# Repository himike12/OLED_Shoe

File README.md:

# OLED_Shoe

This is the git repository for both the mobile application as well as the hardware design and code.

The Hardware file includes all of the files relating to the hardware design as well as the software for the embedded microcontroller.

Dependencies:

Linux
For 64-bit Linux users, libc6:i386, libstdc++6:i386, libncurses5:i386 and libudev1:i386 need to be installed :
  * sudo dpkg --add-architecture i386
  * sudo apt-get update
  * sudo apt-get -y install libc6:i386 libstdc++6:i386 libncurses5:i386 libudev1:i386
  
From the Library Manager:
  * Adafruit_GFX_Library
  * BLEPeripheral
  * PL_microEPD

Programmer:
  * CMSIS-DAP

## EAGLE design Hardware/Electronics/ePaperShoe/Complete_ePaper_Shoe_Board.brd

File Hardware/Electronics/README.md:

File Contents

Adafruit_Designs - Contains the original schematic diagrams and PCB designs for parts that were used in the project. Some of the schematic diagrams have been coped and modified to work in the project.

ePaperShoe - Contains the schematic diagrams and PCB designs created for the project

nRF52_Reference_Scematics - Contains the reference documents for the Nordic nRF52-DK

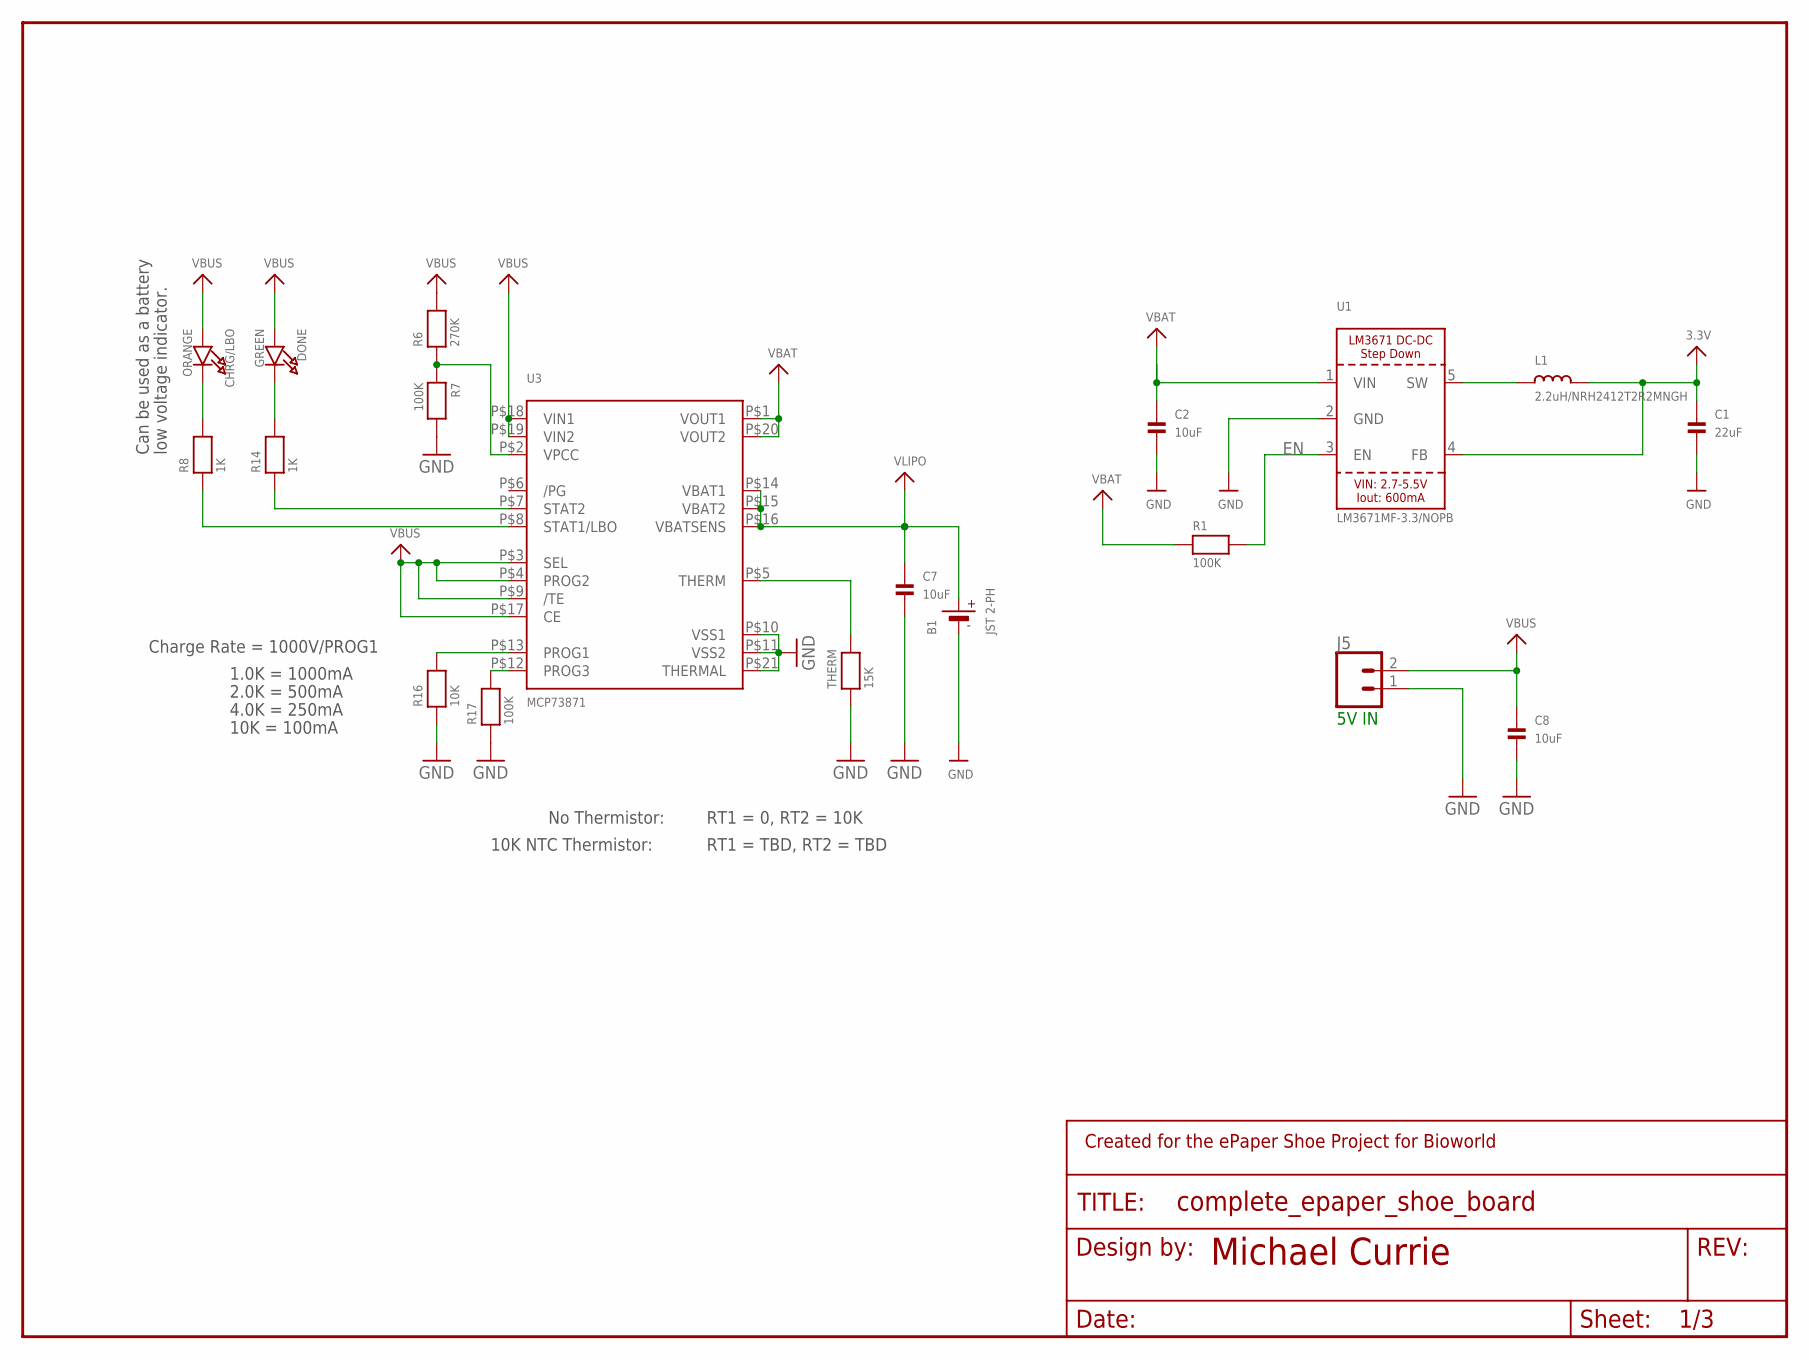
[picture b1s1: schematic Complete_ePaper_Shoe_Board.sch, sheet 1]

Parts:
B1: JST 2-PH; JSTPH2
C1: 22uF; 0805
C2, C7, C8: 10uF; 0805
CHRG/LBO: ORANGE; CHIPLED_0805_NOOUTLINE
DONE: GREEN; CHIPLED_0805_NOOUTLINE
FRAME1: FRAME-LETTER-MICHAELNO_PACKAGE; DUMMY
J5: CONN_02; 1X02
L1: 2.2uH/NRH2412T2R2MNGH; INDUCTOR_5X5MM_NR5040_NOTHERMALS
R1, R7, R17: 100K; 0805
R6: 270K; 0805
R8, R14: 1K; 0805
R16: 10K; 0805
THERM: 15K; 0805
U1: LM3671MF-3.3/NOPB; SOT23-5
U3: MCP73871; QFN20_4MM

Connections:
3.3V: C1.1, L1.P$2 (2), U1.4 (FB); also elsewhere on the board
EN: R1.2, U1.3 (EN)
GND: B1.1 (-), C1.2, C2.2, C7.2, C8.2, J5.1, R7.2, R16.1, R17.1, THERM.1, U1.2 (GND), U3.P$10 (VSS1), U3.P$11 (VSS2), U3.P$21 (THERMAL); also elsewhere on the board
unnamed: L1.P$1 (1), U1.5 (SW)
unnamed: R6.1, R7.1, U3.P$2 (VPCC)
unnamed: DONE.C, R14.2
unnamed: R14.1, U3.P$7 (STAT2)
unnamed: THERM.2, U3.P$5 (THERM)
unnamed: R8.1, U3.P$8 (STAT1/LBO)
unnamed: CHRG/LBO.C, R8.2
unnamed: R17.2, U3.P$12 (PROG3)
unnamed: R16.2, U3.P$13 (PROG1)
VBAT: C2.1, R1.1, U1.1 (VIN), U3.P$1 (VOUT1), U3.P$20 (VOUT2)
VBUS: C8.1, CHRG/LBO.A, DONE.A, J5.2, R6.2, U3.P$3 (SEL), U3.P$4 (PROG2), U3.P$9 (/TE), U3.P$17 (CE), U3.P$18 (VIN1), U3.P$19 (VIN2)
VLIPO: B1.2 (+), C7.1, U3.P$14 (VBAT1), U3.P$15 (VBAT2), U3.P$16 (VBATSENS)

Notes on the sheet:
Charge Rate = 1000V/PROG1
1.0K = 1000mA
2.0K = 500mA
No Thermistor:
10K NTC Thermistor:
RT1 = 0, RT2 = 10K
RT1 = TBD, RT2 = TBD
4.0K = 250mA
10K = 100mA
Can be used as a battery
low voltage indicator.
5V IN

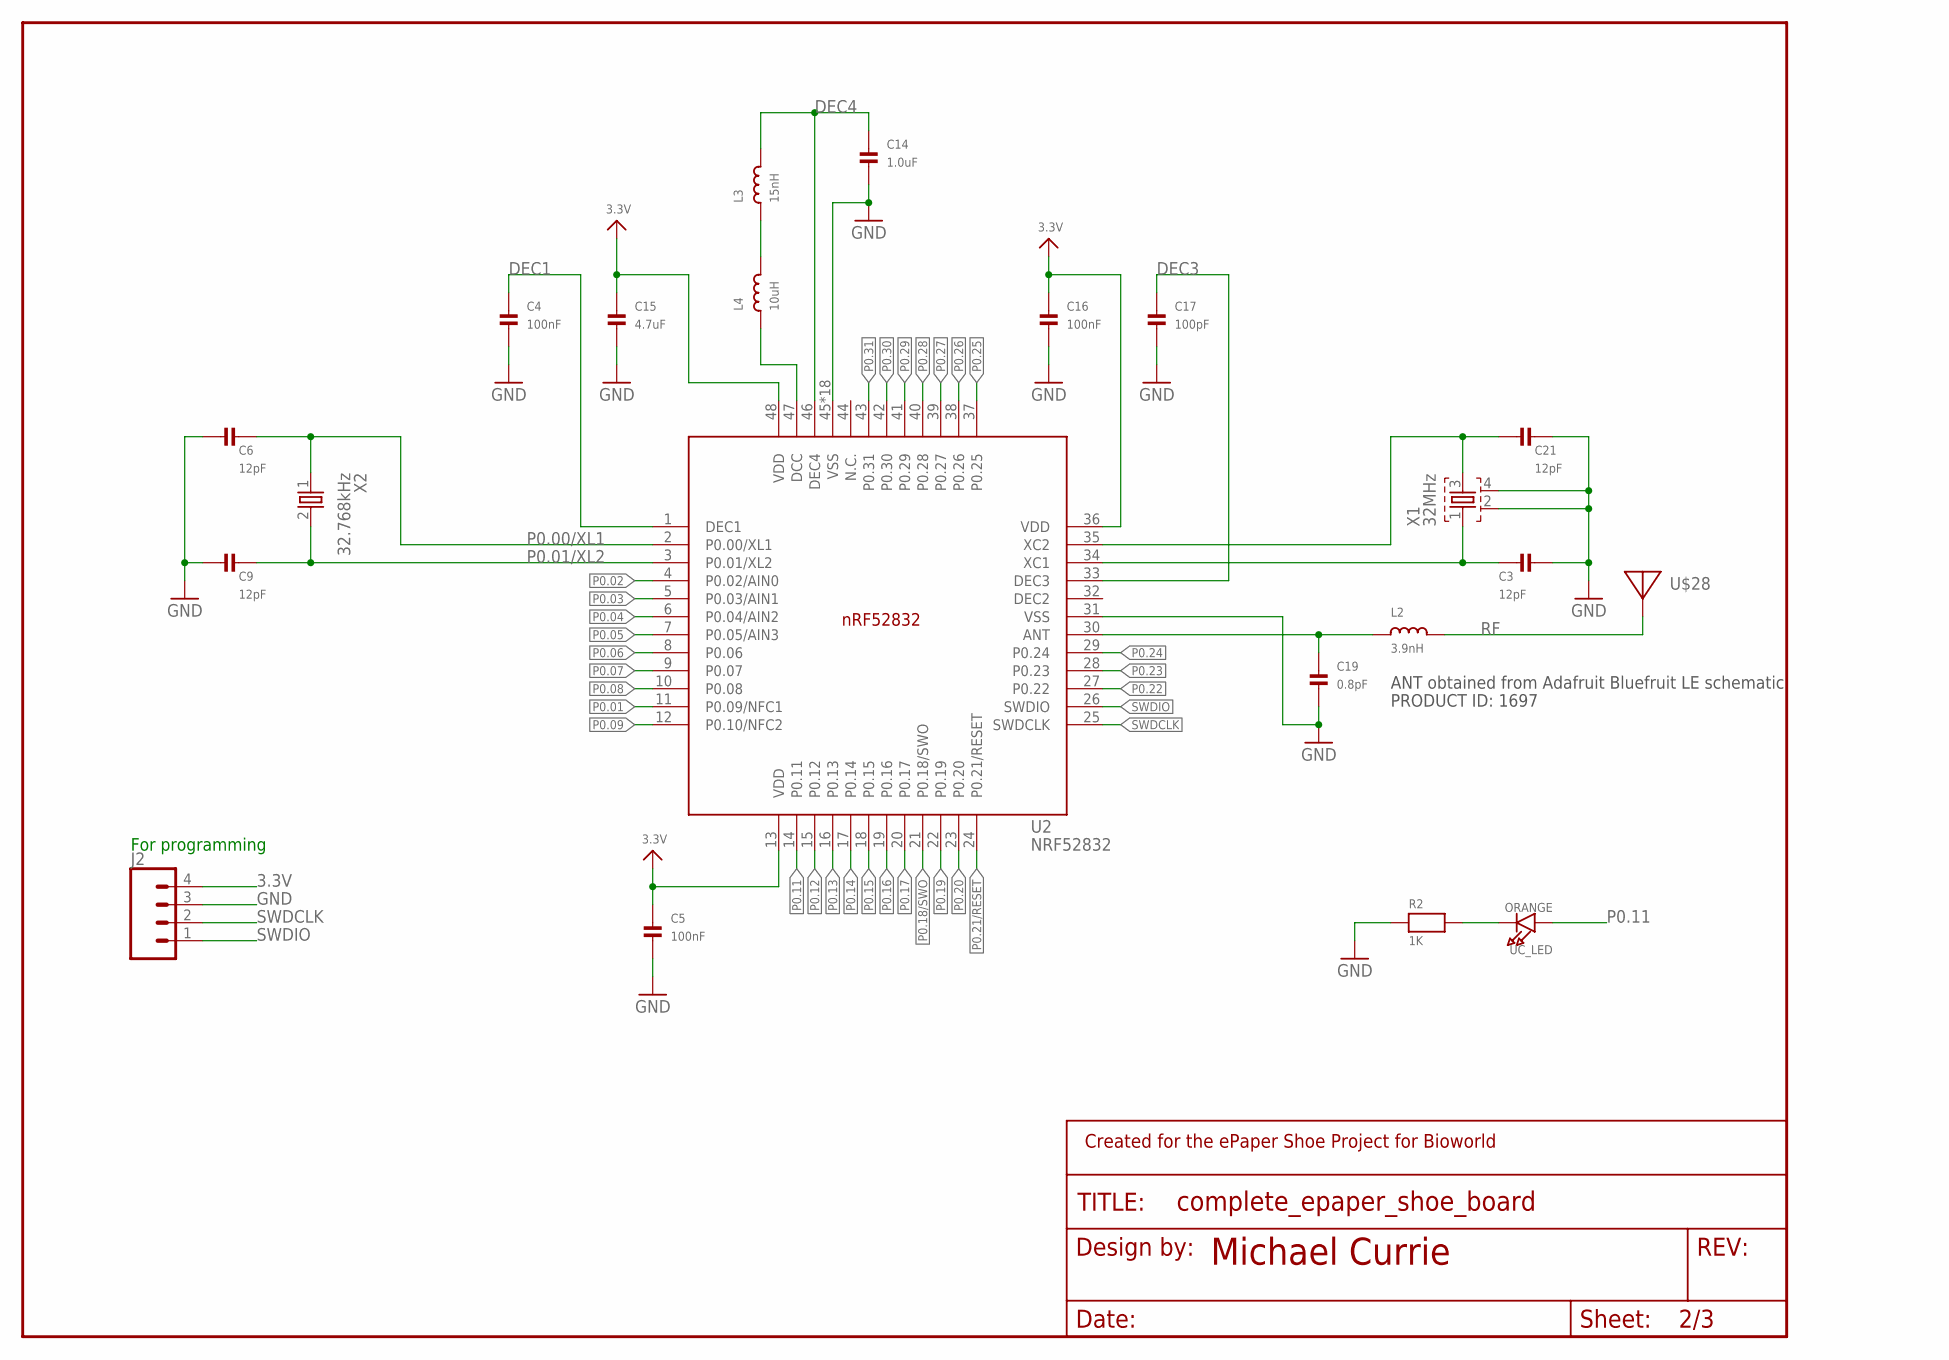
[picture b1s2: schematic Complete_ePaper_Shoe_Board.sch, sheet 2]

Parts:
C3, C6, C9, C21: 12pF; 0805
C4, C5, C16: 100nF; 0805
C14: 1.0uF; 0805
C15: 4.7uF; 0805
C17: 100pF; 0805
C19: 0.8pF; 0805
FRAME2: FRAME-LETTER-MICHAELNO_PACKAGE; DUMMY
J2: CONN_04; 1X04
L2: 3.9nH; 0805
L3: 15nH; 0805
L4: 10uH; 0805
R2: 1K; 0805
U2: NRF52832; QFN40P600X600X90-48_N
U$28: ANTENNA_PCBNRF8001_1.6MM; ANT_PCB_2.4GHZ_NRF8001_1.6MM_1OZ
UC_LED: ORANGE; CHIPLED_0805_NOOUTLINE
X1: 32MHz; BT-XTAL_2016_N
X2: 32.768kHz; XTAL_3215_N

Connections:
3.3V: C5.1, C15.1, C16.1, J2.4, U2.13 (VDD), U2.36 (VDD), U2.48 (VDD); also elsewhere on the board
ANT: C19.1, L2.1, U2.30 (ANT)
DEC1: C4.1, U2.1 (DEC1)
DEC3: C17.1, U2.33 (DEC3)
DEC4: C14.1, L3.2, U2.46 (DEC4)
GND: C3.2, C4.2, C5.2, C6.1, C9.1, C14.2, C15.2, C16.2, C17.2, C19.2, C21.2, J2.3, R2.1, U2.31 (VSS), U2.45 (VSS), U2.PAD (VSS), U2.PAD@VIA01 (VSS), U2.PAD@VIA02 (VSS), U2.PAD@VIA03 (VSS), U2.PAD@VIA04 (VSS), U2.PAD@VIA05 (VSS), U2.PAD@VIA06 (VSS), U2.PAD@VIA07 (VSS), U2.PAD@VIA08 (VSS), U2.PAD@VIA09 (VSS), U2.PAD@VIA10 (VSS), U2.PAD@VIA11 (VSS), U2.PAD@VIA12 (VSS), U2.PAD@VIA13 (VSS), U2.PAD@VIA14 (VSS), U2.PAD@VIA15 (VSS), U2.PAD@VIA16 (VSS), X1.2, X1.4; also elsewhere on the board
unnamed: L3.1, L4.2
unnamed: C21.1, U2.35 (XC2), X1.3
unnamed: L4.1, U2.47 (DCC)
unnamed: R2.2, UC_LED.C
P0.00/XL1: C6.2, U2.2 (P0.00/XL1), X2.1
P0.01: U2.11 (P0.09/NFC1)
P0.01/XL2: C9.2, U2.3 (P0.01/XL2), X2.2
P0.02: U2.4 (P0.02/AIN0)
P0.03: U2.5 (P0.03/AIN1)
P0.04: U2.6 (P0.04/AIN2)
P0.05: U2.7 (P0.05/AIN3)
P0.06: U2.8 (P0.06)
P0.07: U2.9 (P0.07)
P0.08: U2.10 (P0.08)
P0.09: U2.12 (P0.10/NFC2)
P0.11: U2.14 (P0.11), UC_LED.A
P0.12: U2.15 (P0.12)
P0.13: U2.16 (P0.13)
P0.14: U2.17 (P0.14)
P0.15: U2.18 (P0.15)
P0.16: U2.19 (P0.16)
P0.17: U2.20 (P0.17)
P0.18/SWO: U2.21 (P0.18/SWO)
P0.19: U2.22 (P0.19)
P0.20: U2.23 (P0.20)
P0.21/RESET: U2.24 (P0.21/RESET)
P0.22: U2.27 (P0.22); also elsewhere on the board
P0.23: U2.28 (P0.23); also elsewhere on the board
P0.24: U2.29 (P0.24); also elsewhere on the board
P0.25: U2.37 (P0.25); also elsewhere on the board
P0.26: U2.38 (P0.26)
P0.27: U2.39 (P0.27)
P0.28: U2.40 (P0.28)
P0.29: U2.41 (P0.29)
P0.30: U2.42 (P0.30); also elsewhere on the board
P0.31: U2.43 (P0.31); also elsewhere on the board
RF: L2.2, U$28.FEED
SWDCLK: J2.2, U2.25 (SWDCLK)
SWDIO: J2.1, U2.26 (SWDIO)
X1: C3.1, U2.34 (XC1), X1.1

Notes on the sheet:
ANT obtained from Adafruit Bluefruit LE schematic
PRODUCT ID: 1697
For programming

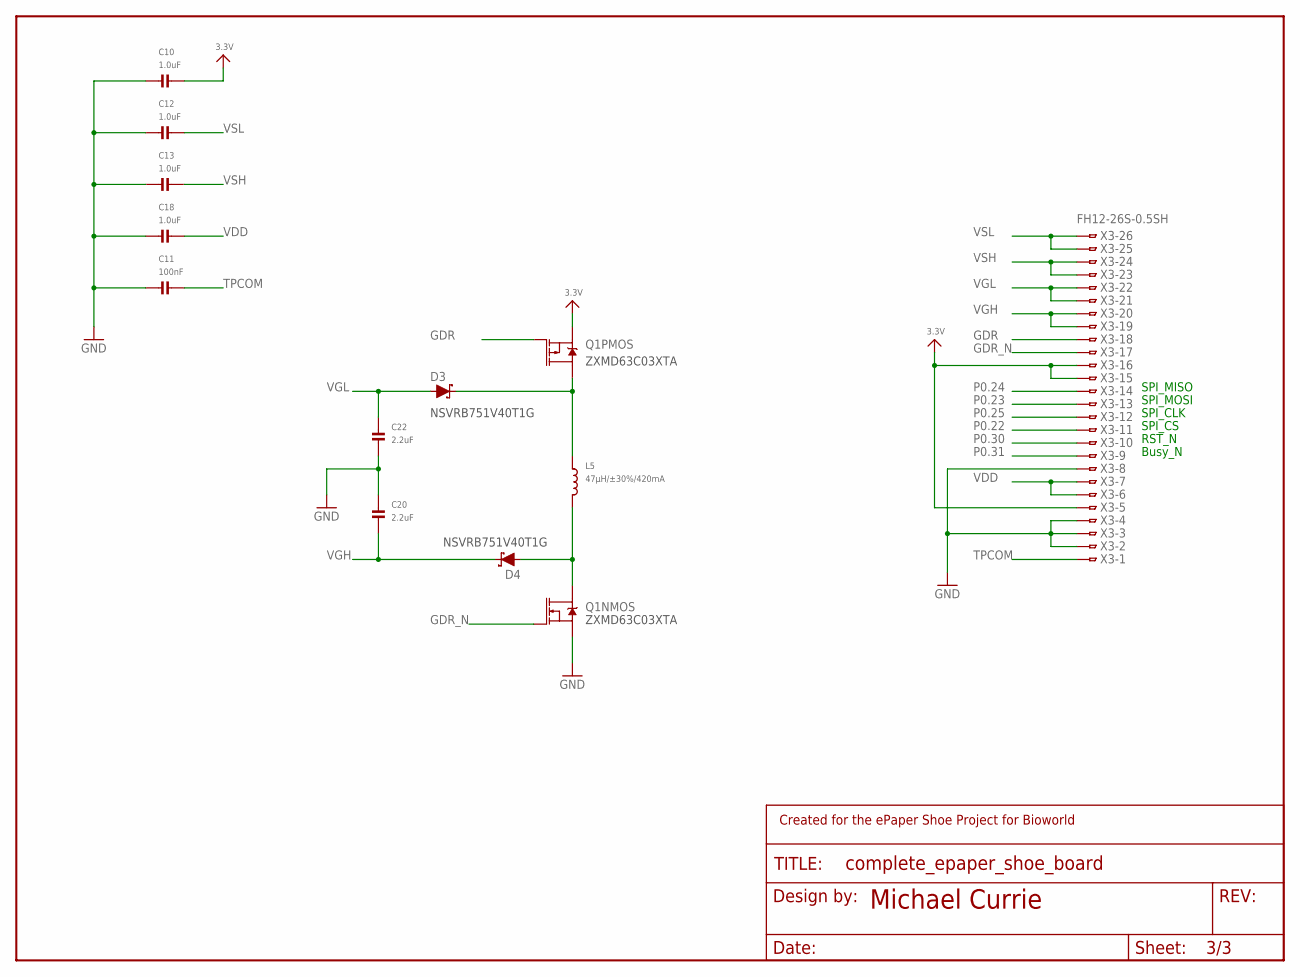
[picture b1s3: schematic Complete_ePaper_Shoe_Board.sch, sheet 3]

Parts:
C10, C12, C13, C18: 1.0uF; 0805
C11: 100nF; 0805
C20, C22: 2.2uF; 0805
D3, D4: 0.5A/40V/420mV; SOD-323
FRAME3: FRAME-LETTER-MICHAELNO_PACKAGE; DUMMY
L5: 47µH/±30%/420mA; INDUCTOR_5X5MM_NR5040_NOTHERMALS
Q1: IRF7509; MSOP8
X3: FH12-26S-0.5SH

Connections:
3.3V: C10.2, Q1.3 (S), X3.5, X3.15, X3.16; also elsewhere on the board
GDR: Q1.4 (G), X3.18
GDR_N: Q1.2 (G), X3.17
GND: C10.1, C11.1, C12.1, C13.1, C18.1, C20.1, C22.2, Q1.1 (S), X3.2, X3.3, X3.4, X3.8; also elsewhere on the board
unnamed: D3.C, L5.P$1 (1), Q1.5 (D), Q1.6 (D)
unnamed: D4.A, L5.P$2 (2), Q1.7 (D), Q1.8 (D)
P0.22: X3.11; also elsewhere on the board
P0.23: X3.13; also elsewhere on the board
P0.24: X3.14; also elsewhere on the board
P0.25: X3.12; also elsewhere on the board
P0.30: X3.10; also elsewhere on the board
P0.31: X3.9; also elsewhere on the board
TPCOM: C11.2, X3.1
VDD: C18.2, X3.6, X3.7
VGH: C20.2, D4.C, X3.19, X3.20
VGL: C22.1, D3.A, X3.21, X3.22
VSH: C13.2, X3.23, X3.24
VSL: C12.2, X3.25, X3.26

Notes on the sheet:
ZXMD63C03XTA
NSVRB751V40T1G
SPI_CLK
SPI_MOSI
SPI_CS
SPI_MISO
Busy_N
RST_N

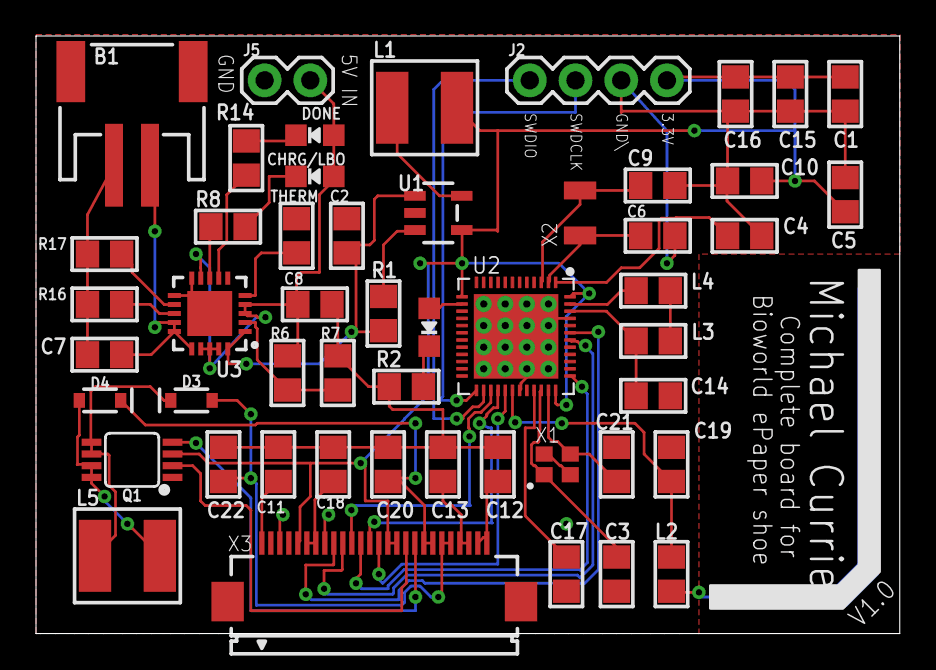
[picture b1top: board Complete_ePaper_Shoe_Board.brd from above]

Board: 2 copper layers, 48.0 x 33.2 mm, 55 parts (1 on the bottom side), 46 nets.

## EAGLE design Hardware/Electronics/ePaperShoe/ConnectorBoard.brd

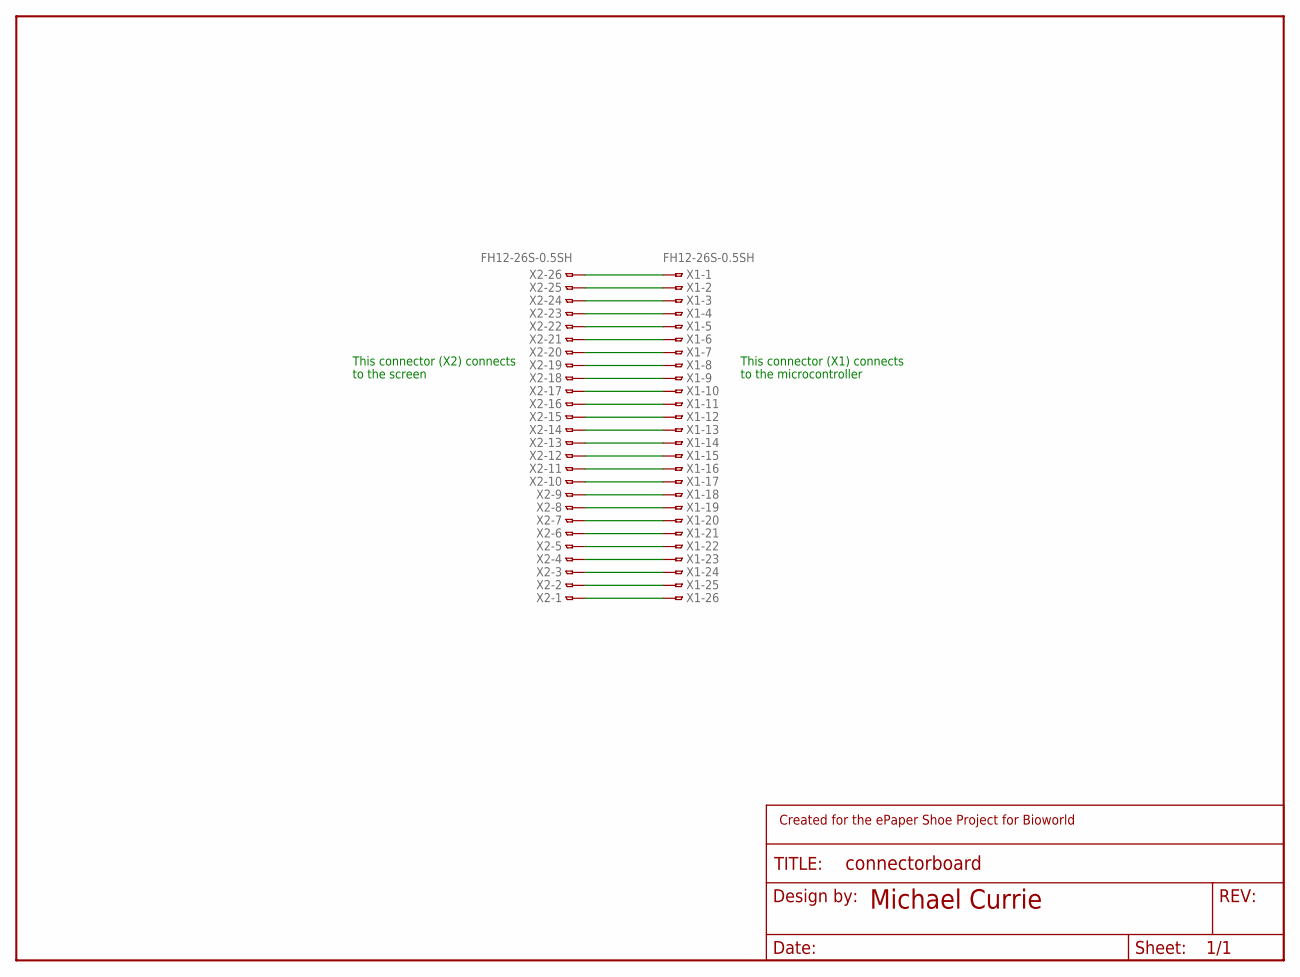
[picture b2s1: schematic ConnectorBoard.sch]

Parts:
FRAME1: FRAME-LETTER-MICHAELNO_PACKAGE; DUMMY
X1, X2: FH12-26S-0.5SH

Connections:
unnamed: X1.26, X2.1
unnamed: X1.18, X2.9
unnamed: X1.23, X2.4
unnamed: X1.24, X2.3
unnamed: X1.22, X2.5
unnamed: X1.21, X2.6
unnamed: X1.20, X2.7
unnamed: X1.25, X2.2
unnamed: X1.19, X2.8
unnamed: X1.17, X2.10
unnamed: X1.16, X2.11
unnamed: X1.15, X2.12
unnamed: X1.14, X2.13
unnamed: X1.13, X2.14
unnamed: X1.12, X2.15
unnamed: X1.11, X2.16
unnamed: X1.10, X2.17
unnamed: X1.9, X2.18
unnamed: X1.2, X2.25
unnamed: X1.7, X2.20
unnamed: X1.6, X2.21
unnamed: X1.5, X2.22
unnamed: X1.3, X2.24
unnamed: X1.4, X2.23
unnamed: X1.8, X2.19
unnamed: X1.1, X2.26

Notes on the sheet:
to the screen
This connector (X2) connects
to the microcontroller
This connector (X1) connects

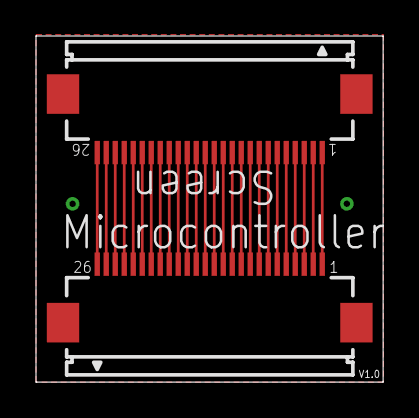
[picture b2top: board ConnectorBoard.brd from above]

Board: 2 copper layers, 19.3 x 19.2 mm, 3 parts (0 on the bottom side), 26 nets.

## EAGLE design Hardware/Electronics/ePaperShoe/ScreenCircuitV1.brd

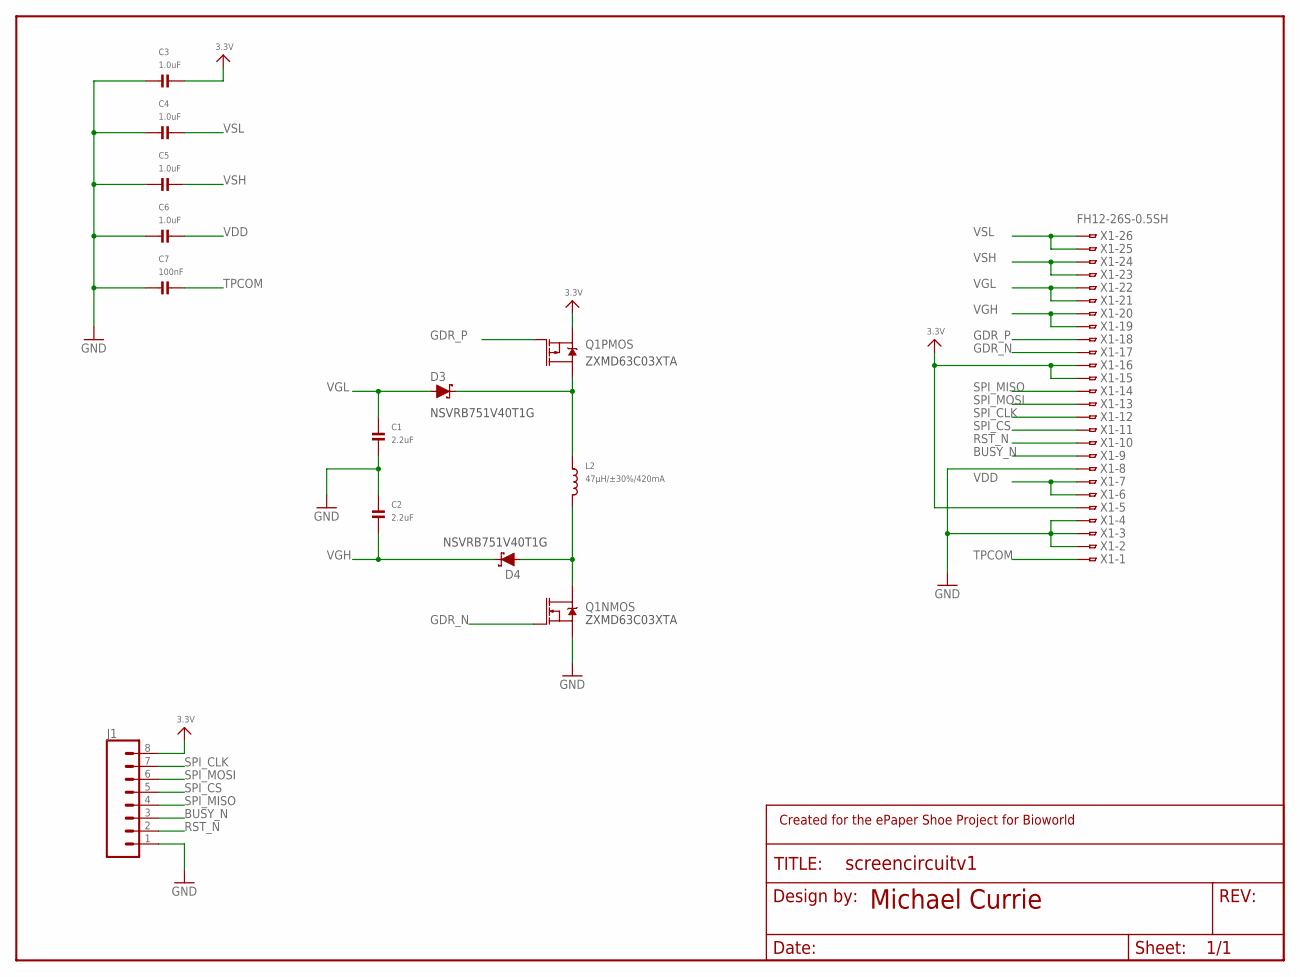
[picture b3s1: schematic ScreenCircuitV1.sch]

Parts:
C1, C2: 2.2uF; 0805
C3, C4, C5, C6: 1.0uF; 0805
C7: 100nF; 0805
D3, D4: 0.5A/40V/420mV; SOD-323
FRAME1: FRAME-LETTER-MICHAELNO_PACKAGE; DUMMY
J1: 1X08
L2: 47µH/±30%/420mA; INDUCTOR_5X5MM_NR5040_NOTHERMALS
Q1: IRF7509; MSOP8
X1: FH12-26S-0.5SH

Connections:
3.3V: C3.2, J1.8, Q1.3 (S), X1.5, X1.15, X1.16
BUSY_N: J1.3, X1.9
GDR_N: Q1.2 (G), X1.17
GDR_P: Q1.4 (G), X1.18
GND: C1.2, C2.1, C3.1, C4.1, C5.1, C6.1, C7.1, J1.1, Q1.1 (S), X1.2, X1.3, X1.4, X1.8
unnamed: D3.C, L2.P$1 (1), Q1.5 (D), Q1.6 (D)
unnamed: D4.A, L2.P$2 (2), Q1.7 (D), Q1.8 (D)
RST_N: J1.2, X1.10
SPI_CLK: J1.7, X1.12
SPI_CS: J1.5, X1.11
SPI_MISO: J1.4, X1.14
SPI_MOSI: J1.6, X1.13
TPCOM: C7.2, X1.1
VDD: C6.2, X1.6, X1.7
VGH: C2.2, D4.C, X1.19, X1.20
VGL: C1.1, D3.A, X1.21, X1.22
VSH: C5.2, X1.23, X1.24
VSL: C4.2, X1.25, X1.26

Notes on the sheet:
ZXMD63C03XTA
NSVRB751V40T1G

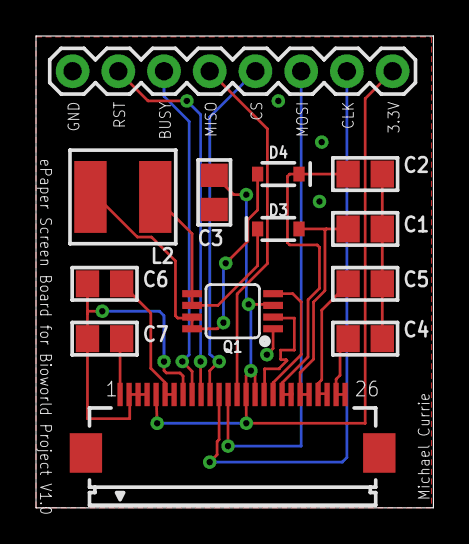
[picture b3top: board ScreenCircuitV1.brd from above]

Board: 2 copper layers, 22.1 x 26.2 mm, 14 parts (0 on the bottom side), 18 nets.

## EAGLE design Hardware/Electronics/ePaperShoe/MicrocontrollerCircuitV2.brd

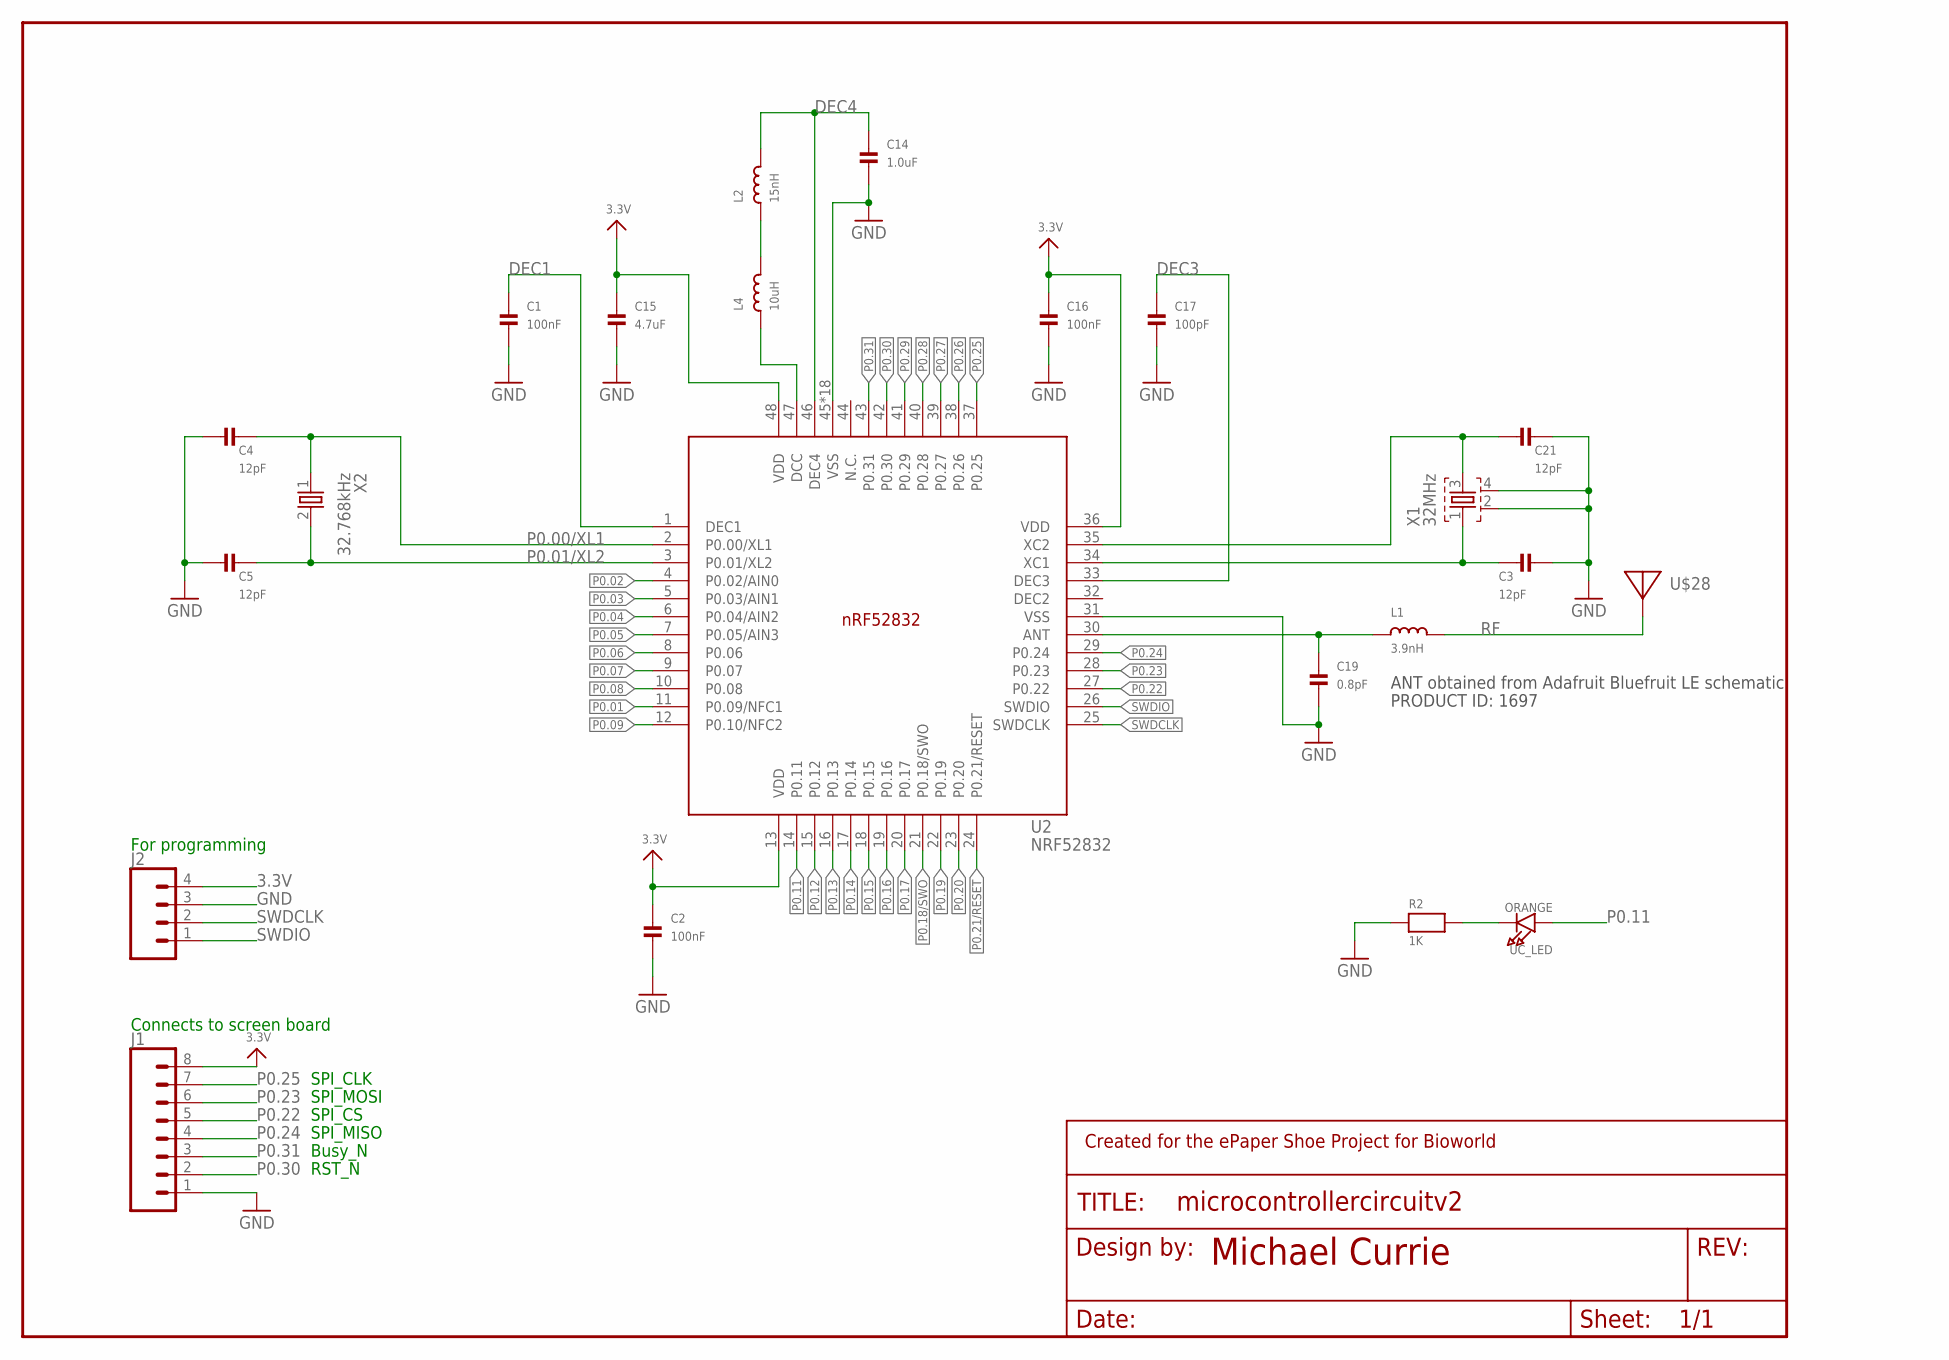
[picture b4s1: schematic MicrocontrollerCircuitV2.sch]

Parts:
C1, C2, C16: 100nF; 0805
C3, C4, C5, C21: 12pF; 0805
C14: 1.0uF; 0805
C15: 4.7uF; 0805
C17: 100pF; 0805
C19: 0.8pF; 0805
FRAME2: FRAME-LETTER-MICHAELNO_PACKAGE; DUMMY
J1: CONN_08"; 1X08
J2: CONN_04; 1X04
L1: 3.9nH; 0805
L2: 15nH; 0805
L4: 10uH; 0805
R2: 1K; 0805
U2: NRF52832; QFN40P600X600X90-48_N
U$28: ANTENNA_PCBNRF8001_1.6MM; ANT_PCB_2.4GHZ_NRF8001_1.6MM_1OZ
UC_LED: ORANGE; CHIPLED_0805_NOOUTLINE
X1: 32MHz; BT-XTAL_2016_N
X2: 32.768kHz; XTAL_3215_N

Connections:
3.3V: C2.1, C15.1, C16.1, J1.8, J2.4, U2.13 (VDD), U2.36 (VDD), U2.48 (VDD)
ANT: C19.1, L1.1, U2.30 (ANT)
DEC1: C1.1, U2.1 (DEC1)
DEC3: C17.1, U2.33 (DEC3)
DEC4: C14.1, L2.2, U2.46 (DEC4)
GND: C1.2, C2.2, C3.2, C4.1, C5.1, C14.2, C15.2, C16.2, C17.2, C19.2, C21.2, J1.1, J2.3, R2.1, U2.31 (VSS), U2.45 (VSS), U2.PAD (VSS), U2.PAD@VIA01 (VSS), U2.PAD@VIA02 (VSS), U2.PAD@VIA03 (VSS), U2.PAD@VIA04 (VSS), U2.PAD@VIA05 (VSS), U2.PAD@VIA06 (VSS), U2.PAD@VIA07 (VSS), U2.PAD@VIA08 (VSS), U2.PAD@VIA09 (VSS), U2.PAD@VIA10 (VSS), U2.PAD@VIA11 (VSS), U2.PAD@VIA12 (VSS), U2.PAD@VIA13 (VSS), U2.PAD@VIA14 (VSS), U2.PAD@VIA15 (VSS), U2.PAD@VIA16 (VSS), X1.2, X1.4
unnamed: L2.1, L4.2
unnamed: C21.1, U2.35 (XC2), X1.3
unnamed: L4.1, U2.47 (DCC)
unnamed: R2.2, UC_LED.C
P0.00/XL1: C4.2, U2.2 (P0.00/XL1), X2.1
P0.01: U2.11 (P0.09/NFC1)
P0.01/XL2: C5.2, U2.3 (P0.01/XL2), X2.2
P0.02: U2.4 (P0.02/AIN0)
P0.03: U2.5 (P0.03/AIN1)
P0.04: U2.6 (P0.04/AIN2)
P0.05: U2.7 (P0.05/AIN3)
P0.06: U2.8 (P0.06)
P0.07: U2.9 (P0.07)
P0.08: U2.10 (P0.08)
P0.09: U2.12 (P0.10/NFC2)
P0.11: U2.14 (P0.11), UC_LED.A
P0.12: U2.15 (P0.12)
P0.13: U2.16 (P0.13)
P0.14: U2.17 (P0.14)
P0.15: U2.18 (P0.15)
P0.16: U2.19 (P0.16)
P0.17: U2.20 (P0.17)
P0.18/SWO: U2.21 (P0.18/SWO)
P0.19: U2.22 (P0.19)
P0.20: U2.23 (P0.20)
P0.21/RESET: U2.24 (P0.21/RESET)
P0.22: J1.5, U2.27 (P0.22)
P0.23: J1.6, U2.28 (P0.23)
P0.24: J1.4, U2.29 (P0.24)
P0.25: J1.7, U2.37 (P0.25)
P0.26: U2.38 (P0.26)
P0.27: U2.39 (P0.27)
P0.28: U2.40 (P0.28)
P0.29: U2.41 (P0.29)
P0.30: J1.2, U2.42 (P0.30)
P0.31: J1.3, U2.43 (P0.31)
RF: L1.2, U$28.FEED
SWDCLK: J2.2, U2.25 (SWDCLK)
SWDIO: J2.1, U2.26 (SWDIO)
X1: C3.1, U2.34 (XC1), X1.1

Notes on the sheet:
ANT obtained from Adafruit Bluefruit LE schematic
PRODUCT ID: 1697
For programming
Connects to screen board
SPI_CLK
SPI_MOSI
SPI_CS
SPI_MISO
Busy_N
RST_N

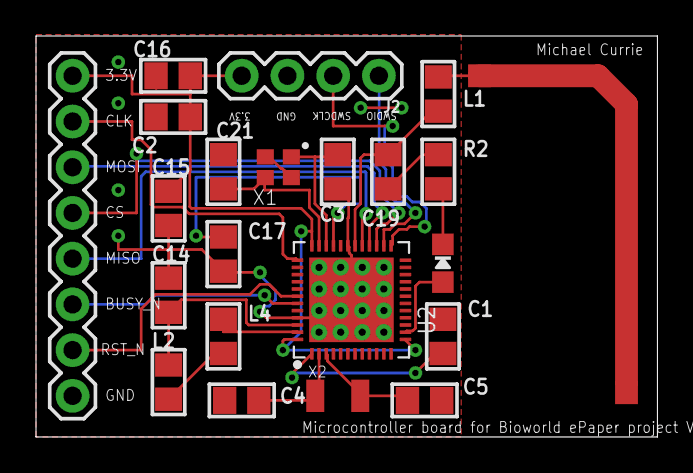
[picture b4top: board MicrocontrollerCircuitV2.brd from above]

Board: 2 copper layers, 34.5 x 22.3 mm, 23 parts (0 on the bottom side), 23 nets.

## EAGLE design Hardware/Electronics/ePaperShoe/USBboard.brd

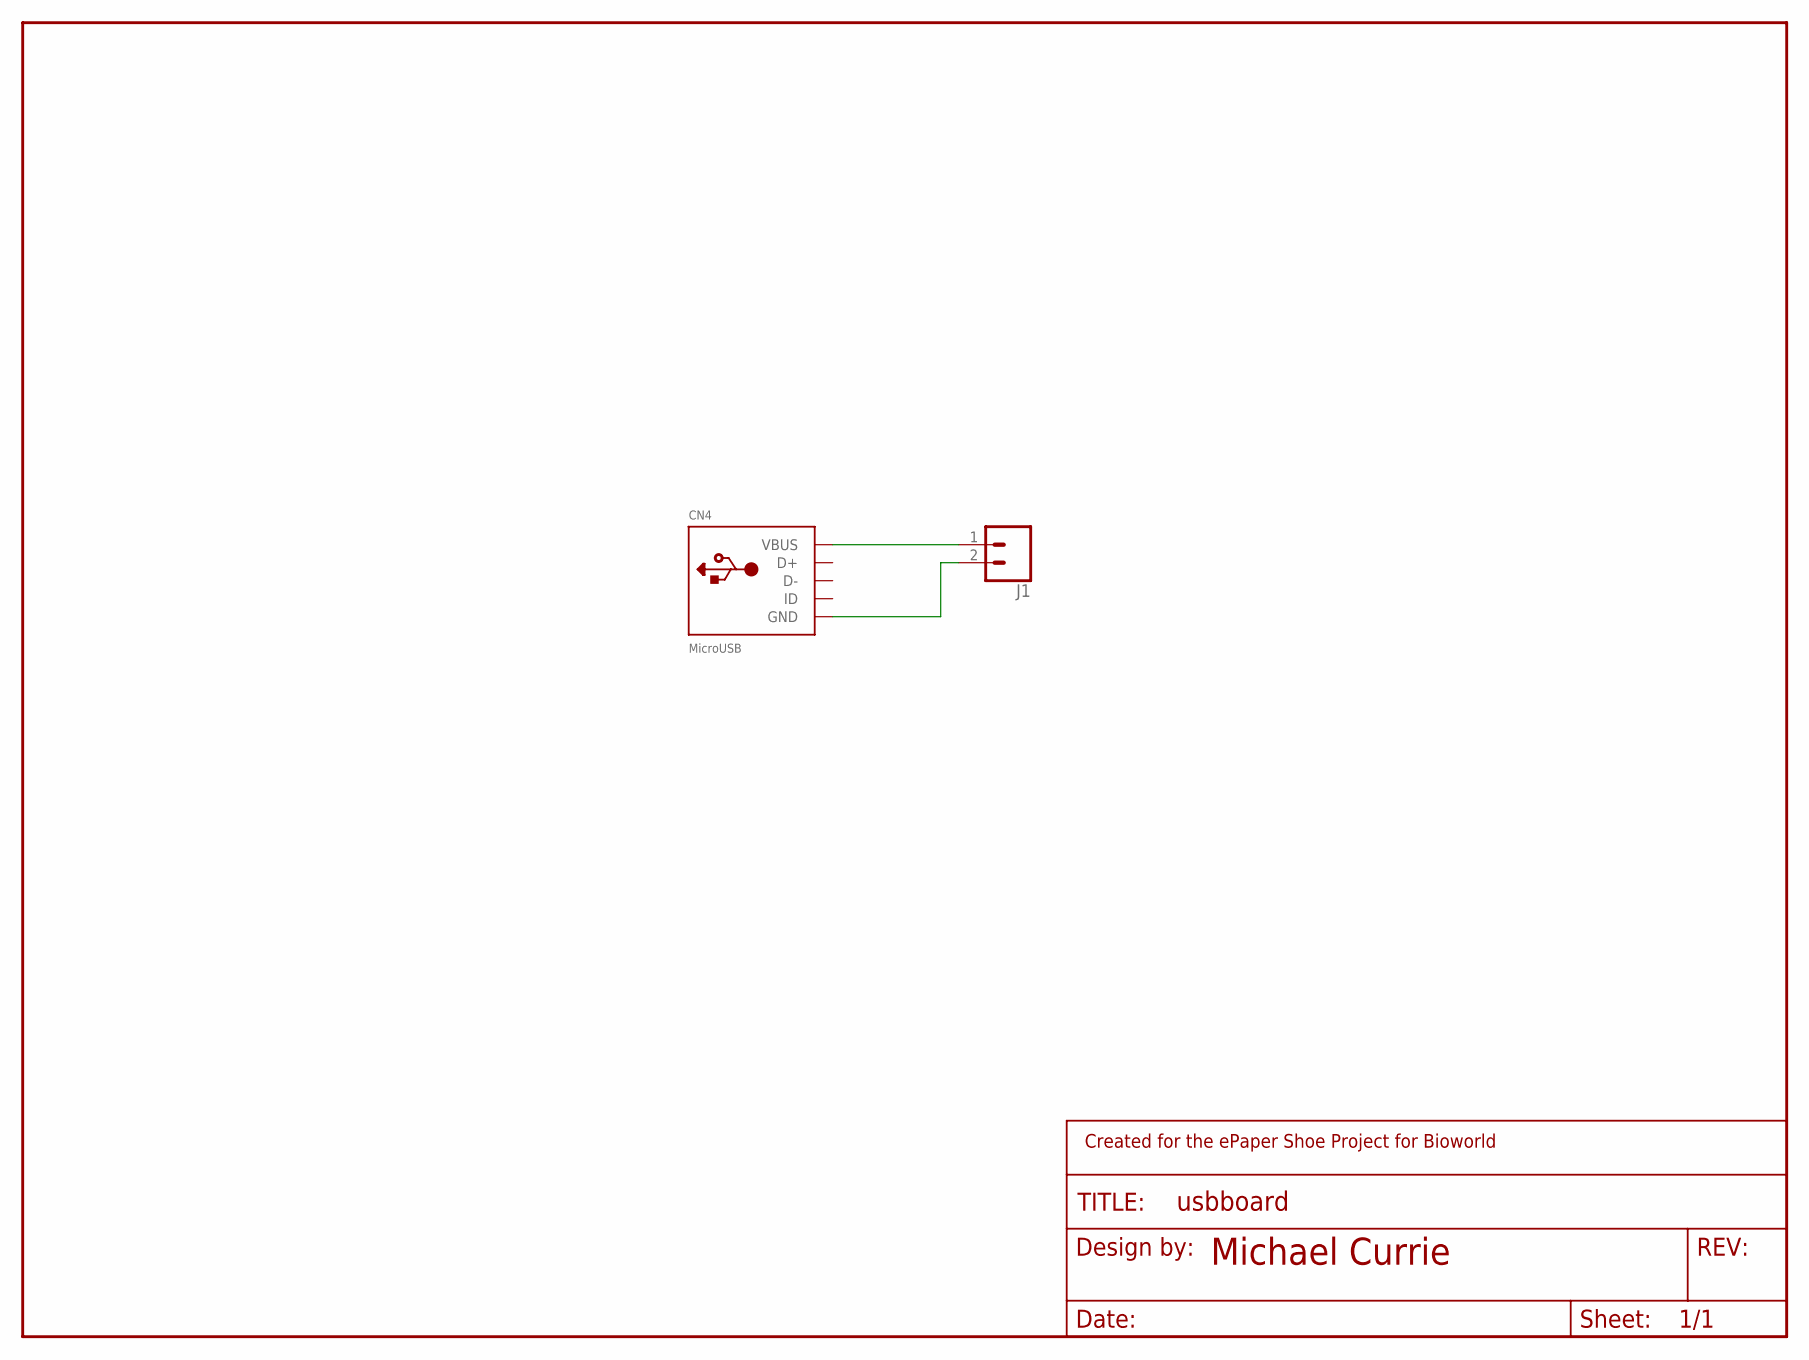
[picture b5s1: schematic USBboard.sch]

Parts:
CN4: MicroUSB; 4UCONN_20329
FRAME1: FRAME-LETTER-MICHAELNO_PACKAGE; DUMMY
J1: CONN_02; 1X02

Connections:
GND: CN4.BASE@1 (GND), CN4.BASE@2 (GND), CN4.GND, CN4.SPRT@1 (GND), CN4.SPRT@2 (GND), CN4.SPRT@3 (GND), CN4.SPRT@4 (GND), J1.2
unnamed: CN4.VBUS, J1.1

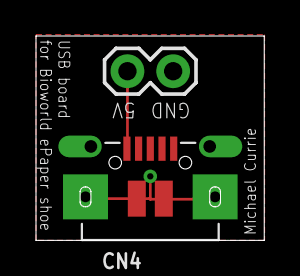
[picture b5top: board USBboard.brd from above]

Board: 2 copper layers, 12.7 x 11.4 mm, 3 parts (0 on the bottom side), 2 nets.

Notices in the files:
parts and their libraries:
microbuilder: This work is placed in the public domain, and may be freely used for commercial and non-commercial work with the following conditions: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
SparkFun-DiscreteSemi: Licensing: Creative Commons ShareAlike 4.0 International - https://creativecommons.org/licenses/by-sa/4.0
